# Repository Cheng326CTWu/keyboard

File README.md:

# 65% keyboard

## Overview

This project was made with the intention of familiarizing myself with the work flow of KiCad. It was also a way to re-learn concepts for schematic captures and the different considerations when laying out a PCB. This repo contains a 65% keyboard PCB design made by referencing tutorials and modifying with new components.

## Software Requirement

* KiCAD

## Tutorial Reference Links

* [RuiQiMao's keyboard tutorial](https://github.com/ruiqimao/keyboard-pcb-guide)
* [ai03's keyboard tutorial](https://wiki.ai03.com/books/pcb-design/page/pcb-guide-part-1---preparations)

## Reference Links

* [Discipline's keyboard repo](https://github.com/coseyfannitutti/discipline)
* [Layer definition in KiCad](https://forum.kicad.info/t/what-is-the-meaning-of-the-layers-in-pcb-new-and-in-the-footprint-editor/9688)
* [BOM in KiCad](https://forum.kicad.info/t/how-to-create-a-bill-of-materials-bom/12346)

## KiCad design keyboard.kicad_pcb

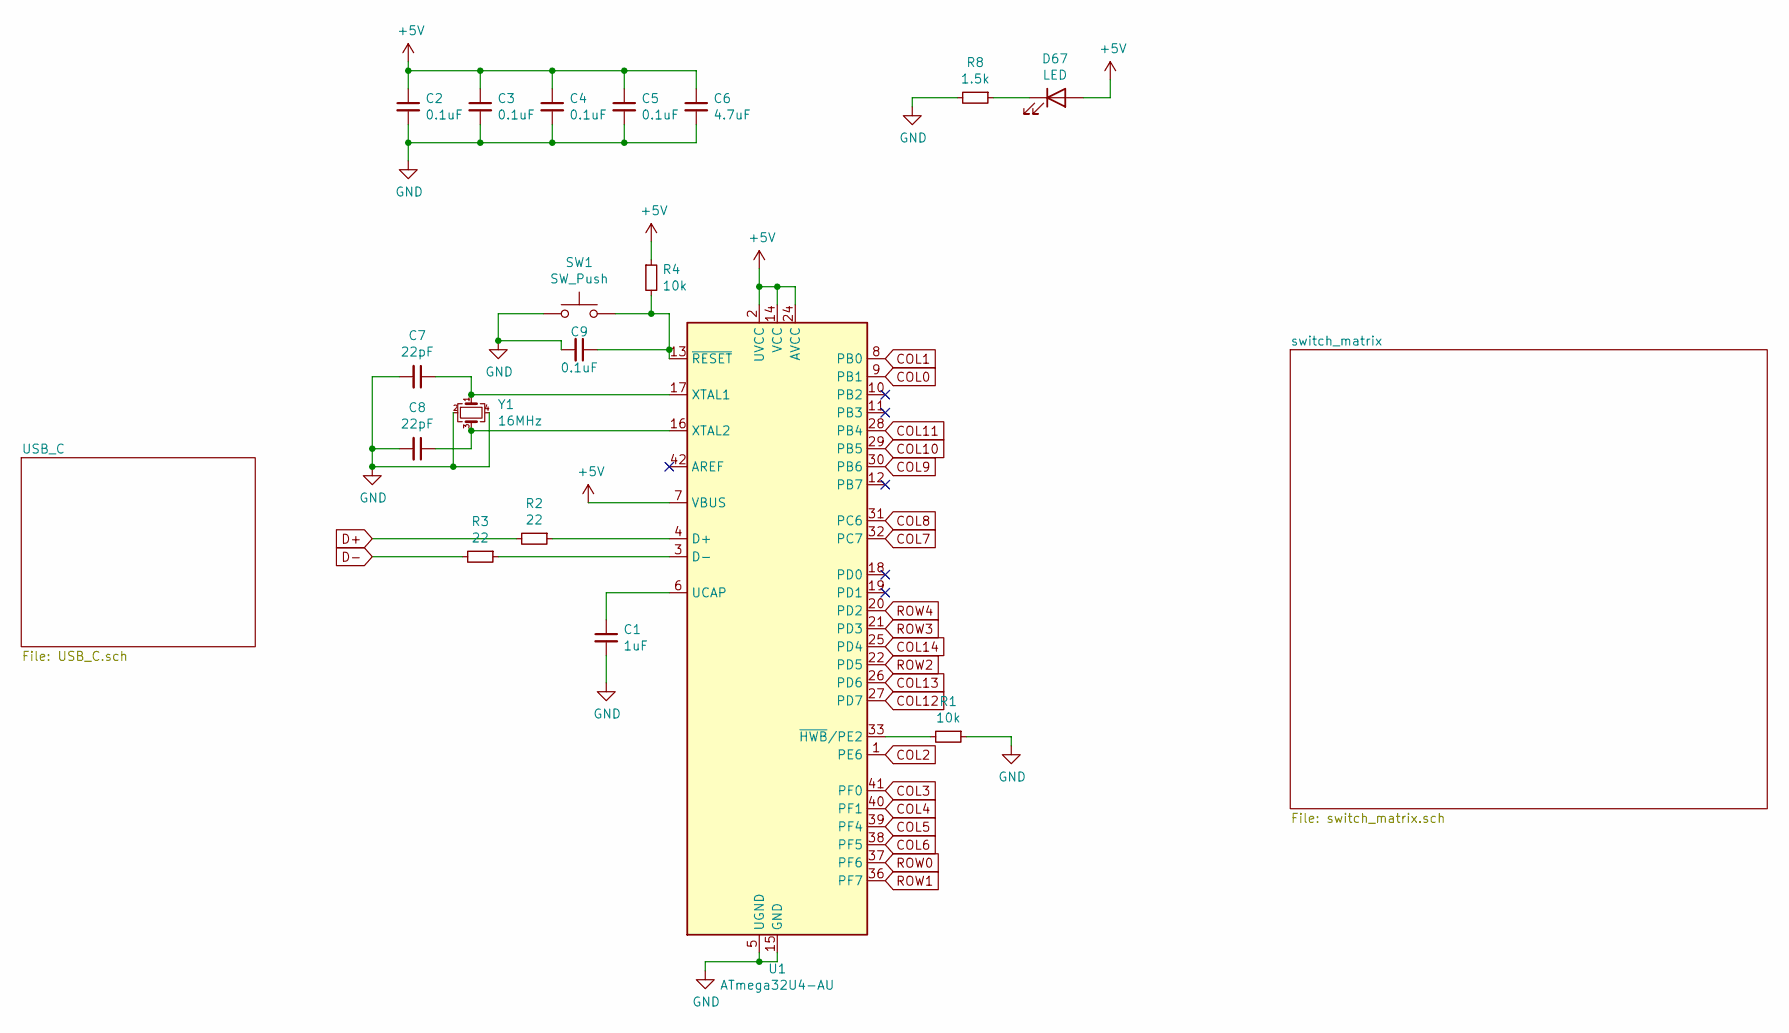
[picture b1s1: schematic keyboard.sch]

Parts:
C1: 1uF; C_0805_2012Metric
C2, C3, C4, C5, C9: 0.1uF; C_0805_2012Metric
C6: 4.7uF; C_0805_2012Metric
C7, C8: 22pF; C_0805_2012Metric
D67: LED; LED_0805_2012Metric
R1, R4: 10k; R_0805_2012Metric
R2, R3: 22; R_0805_2012Metric
R8: 1.5k; R_0805_2012Metric
SW1: SW_Push; SKQG-1155865
U1: ATmega32U4-AU; TQFP-44_10x10mm_P0.8mm
Y1: 16MHz; Crystal_SMD_3225-4Pin_3.2x2.5mm

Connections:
+5V: C2.1, C3.1, C4.1, C5.1, C6.1, D67.2 (A), R4.1, U1.2 (UVCC), U1.7 (VBUS), U1.14 (VCC), U1.24 (AVCC), U1.34 (VCC), U1.44 (AVCC); also elsewhere on the board
COL0: U1.9 (PB1); also elsewhere on the board
COL1: U1.8 (PB0); also elsewhere on the board
COL2: U1.1 (PE6); also elsewhere on the board
COL3: U1.41 (PF0); also elsewhere on the board
COL4: U1.40 (PF1); also elsewhere on the board
COL5: U1.39 (PF4); also elsewhere on the board
COL6: U1.38 (PF5); also elsewhere on the board
COL7: U1.32 (PC7); also elsewhere on the board
COL8: U1.31 (PC6); also elsewhere on the board
COL9: U1.30 (PB6); also elsewhere on the board
COL10: U1.29 (PB5); also elsewhere on the board
COL11: U1.28 (PB4); also elsewhere on the board
COL12: U1.27 (PD7); also elsewhere on the board
COL13: U1.26 (PD6); also elsewhere on the board
COL14: U1.25 (PD4); also elsewhere on the board
D+: R2.2; also elsewhere on the board
D-: R3.2; also elsewhere on the board
GND: C1.2, C2.2, C3.2, C4.2, C5.2, C6.2, C7.2, C8.2, C9.2, R1.1, R8.2, SW1.1, U1.5 (UGND), U1.15 (GND), U1.23 (GND), U1.35 (GND), U1.43 (GND), Y1.2, Y1.4; also elsewhere on the board
unnamed: C1.1, U1.6 (UCAP)
unnamed: C7.1, U1.17 (XTAL1), Y1.1
unnamed: C8.1, U1.16 (XTAL2), Y1.3
unnamed: C9.1, R4.2, SW1.2, U1.13 (~RESET)
unnamed: D67.1 (K), R8.1
unnamed: R1.2, U1.33 (~HWB~/PE2)
unnamed: R2.1, U1.4 (D+)
unnamed: R3.1, U1.3 (D-)
ROW0: U1.37 (PF6); also elsewhere on the board
ROW1: U1.36 (PF7); also elsewhere on the board
ROW2: U1.22 (PD5); also elsewhere on the board
ROW3: U1.21 (PD3); also elsewhere on the board
ROW4: U1.20 (PD2); also elsewhere on the board

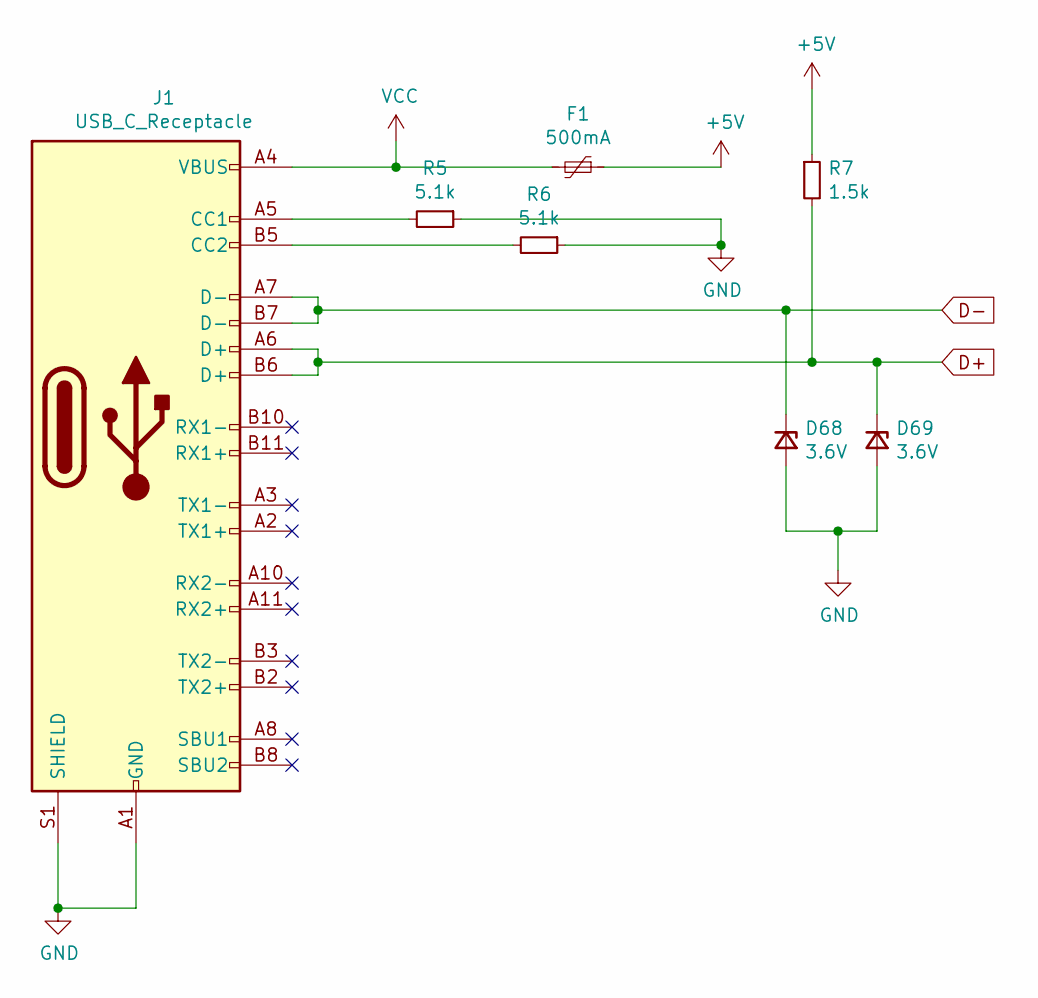
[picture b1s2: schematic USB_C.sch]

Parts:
D68, D69: 3.6V; D_0805_2012Metric
F1: 500mA; Fuse_1206_3216Metric
J1: USB_C_Receptacle; USB_C_Receptacle_GCT_USB4085
R5, R6: 5.1k; R_0805_2012Metric
R7: 1.5k; R_0805_2012Metric

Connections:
+5V: F1.1, R7.1; also elsewhere on the board
D+: D69.1 (K), J1.A6 (D+), J1.B6 (D+), R7.2; also elsewhere on the board
D-: D68.1 (K), J1.A7 (D-), J1.B7 (D-); also elsewhere on the board
GND: D68.2 (A), D69.2 (A), J1.A1 (GND), J1.A12 (GND), J1.B1 (GND), J1.B12 (GND), J1.S1 (SHIELD), R5.1, R6.1; also elsewhere on the board
unnamed: J1.A5 (CC1), R5.2
unnamed: J1.B5 (CC2), R6.2
VCC: F1.2, J1.A4 (VBUS), J1.A9 (VBUS), J1.B4 (VBUS), J1.B9 (VBUS)

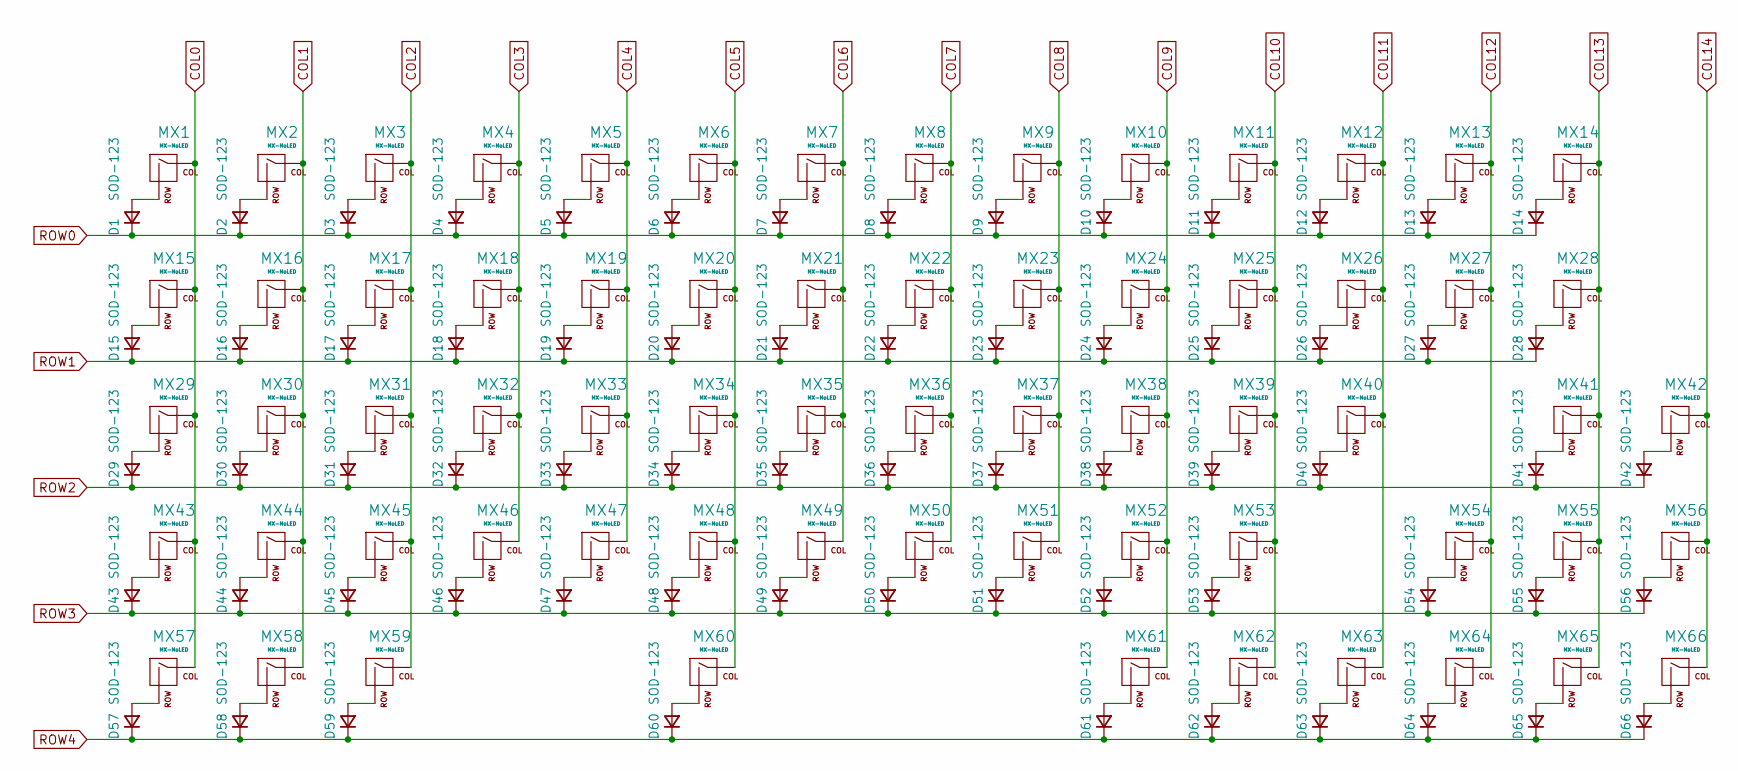
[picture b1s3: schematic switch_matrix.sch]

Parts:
D1, D2, D3, D4, D5, D6, D7, D8, D9, D10, D11, D12, D13, D14, D15, D16, D17, D18, D19, D20, D21, D22, D23, D24, D25, D26, D27, D28, D29, D30, D31, D32, D33, D34, D35, D36, D37, D38, D39, D40, D41, D42, D43, D44, D45, D46, D47, D48, D49, D50, D51, D52, D53, D54, D55, D56, D57, D58, D59, D60, D61, D62, D63, D64, D65, D66: SOD-123; D_SOD-123
MX1, MX2, MX3, MX4, MX5, MX6, MX7, MX8, MX9, MX10, MX11, MX12, MX13, MX16, MX17, MX18, MX19, MX20, MX21, MX22, MX23, MX24, MX25, MX26, MX27, MX30, MX31, MX32, MX33, MX34, MX35, MX36, MX37, MX38, MX39, MX40, MX42, MX44, MX45, MX46, MX47, MX48, MX49, MX50, MX51, MX52, MX53, MX55, MX56, MX58, MX64, MX65, MX66: MX-NoLED; MXOnly-1U-Hotswap
MX14: MX-NoLED; MXOnly-2U-Hotswap
MX15, MX28: MX-NoLED; MXOnly-1.5U-Hotswap
MX29: MX-NoLED; MXOnly-1.75U-Hotswap
MX41, MX43, MX54: MX-NoLED; MXOnly-2.25U-Hotswap
MX57, MX59, MX61, MX62, MX63: MX-NoLED; MXOnly-1.25U-Hotswap
MX60: MX-NoLED; MXOnly-6.25U-Hotswap

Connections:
COL0: MX1.1 (COL), MX15.1 (COL), MX29.1 (COL), MX43.1 (COL), MX57.1 (COL); also elsewhere on the board
COL1: MX2.1 (COL), MX16.1 (COL), MX30.1 (COL), MX44.1 (COL), MX58.1 (COL); also elsewhere on the board
COL2: MX3.1 (COL), MX17.1 (COL), MX31.1 (COL), MX45.1 (COL), MX59.1 (COL); also elsewhere on the board
COL3: MX4.1 (COL), MX18.1 (COL), MX32.1 (COL), MX46.1 (COL); also elsewhere on the board
COL4: MX5.1 (COL), MX19.1 (COL), MX33.1 (COL), MX47.1 (COL); also elsewhere on the board
COL5: MX6.1 (COL), MX20.1 (COL), MX34.1 (COL), MX48.1 (COL), MX60.1 (COL); also elsewhere on the board
COL6: MX7.1 (COL), MX21.1 (COL), MX35.1 (COL), MX49.1 (COL); also elsewhere on the board
COL7: MX8.1 (COL), MX22.1 (COL), MX36.1 (COL), MX50.1 (COL); also elsewhere on the board
COL8: MX9.1 (COL), MX23.1 (COL), MX37.1 (COL), MX51.1 (COL); also elsewhere on the board
COL9: MX10.1 (COL), MX24.1 (COL), MX38.1 (COL), MX52.1 (COL), MX61.1 (COL); also elsewhere on the board
COL10: MX11.1 (COL), MX25.1 (COL), MX39.1 (COL), MX53.1 (COL), MX62.1 (COL); also elsewhere on the board
COL11: MX12.1 (COL), MX26.1 (COL), MX40.1 (COL), MX63.1 (COL); also elsewhere on the board
COL12: MX13.1 (COL), MX27.1 (COL), MX54.1 (COL), MX64.1 (COL); also elsewhere on the board
COL13: MX14.1 (COL), MX28.1 (COL), MX41.1 (COL), MX55.1 (COL), MX65.1 (COL); also elsewhere on the board
COL14: MX42.1 (COL), MX56.1 (COL), MX66.1 (COL); also elsewhere on the board
unnamed: D1.2 (A), MX1.2 (ROW)
unnamed: D2.2 (A), MX2.2 (ROW)
unnamed: D3.2 (A), MX3.2 (ROW)
unnamed: D4.2 (A), MX4.2 (ROW)
unnamed: D5.2 (A), MX5.2 (ROW)
unnamed: D6.2 (A), MX6.2 (ROW)
unnamed: D7.2 (A), MX7.2 (ROW)
unnamed: D8.2 (A), MX8.2 (ROW)
unnamed: D9.2 (A), MX9.2 (ROW)
unnamed: D10.2 (A), MX10.2 (ROW)
unnamed: D11.2 (A), MX11.2 (ROW)
unnamed: D12.2 (A), MX12.2 (ROW)
unnamed: D13.2 (A), MX13.2 (ROW)
unnamed: D14.2 (A), MX14.2 (ROW)
unnamed: D15.2 (A), MX15.2 (ROW)
unnamed: D16.2 (A), MX16.2 (ROW)
unnamed: D17.2 (A), MX17.2 (ROW)
unnamed: D18.2 (A), MX18.2 (ROW)
unnamed: D19.2 (A), MX19.2 (ROW)
unnamed: D20.2 (A), MX20.2 (ROW)
unnamed: D21.2 (A), MX21.2 (ROW)
unnamed: D22.2 (A), MX22.2 (ROW)
unnamed: D23.2 (A), MX23.2 (ROW)
unnamed: D24.2 (A), MX24.2 (ROW)
unnamed: D25.2 (A), MX25.2 (ROW)
unnamed: D26.2 (A), MX26.2 (ROW)
unnamed: D27.2 (A), MX27.2 (ROW)
unnamed: D28.2 (A), MX28.2 (ROW)
unnamed: D29.2 (A), MX29.2 (ROW)
unnamed: D30.2 (A), MX30.2 (ROW)
unnamed: D31.2 (A), MX31.2 (ROW)
unnamed: D32.2 (A), MX32.2 (ROW)
unnamed: D33.2 (A), MX33.2 (ROW)
unnamed: D34.2 (A), MX34.2 (ROW)
unnamed: D35.2 (A), MX35.2 (ROW)
unnamed: D36.2 (A), MX36.2 (ROW)
unnamed: D37.2 (A), MX37.2 (ROW)
unnamed: D38.2 (A), MX38.2 (ROW)
unnamed: D39.2 (A), MX39.2 (ROW)
unnamed: D40.2 (A), MX40.2 (ROW)
unnamed: D41.2 (A), MX41.2 (ROW)
unnamed: D42.2 (A), MX42.2 (ROW)
unnamed: D43.2 (A), MX43.2 (ROW)
unnamed: D44.2 (A), MX44.2 (ROW)
unnamed: D45.2 (A), MX45.2 (ROW)
unnamed: D46.2 (A), MX46.2 (ROW)
unnamed: D47.2 (A), MX47.2 (ROW)
unnamed: D48.2 (A), MX48.2 (ROW)
unnamed: D49.2 (A), MX49.2 (ROW)
unnamed: D50.2 (A), MX50.2 (ROW)
unnamed: D51.2 (A), MX51.2 (ROW)
unnamed: D52.2 (A), MX52.2 (ROW)
unnamed: D53.2 (A), MX53.2 (ROW)
unnamed: D54.2 (A), MX54.2 (ROW)
unnamed: D55.2 (A), MX55.2 (ROW)
unnamed: D56.2 (A), MX56.2 (ROW)
unnamed: D57.2 (A), MX57.2 (ROW)
unnamed: D58.2 (A), MX58.2 (ROW)
unnamed: D59.2 (A), MX59.2 (ROW)
unnamed: D60.2 (A), MX60.2 (ROW)
unnamed: D61.2 (A), MX61.2 (ROW)
unnamed: D62.2 (A), MX62.2 (ROW)
unnamed: D63.2 (A), MX63.2 (ROW)
unnamed: D64.2 (A), MX64.2 (ROW)
unnamed: D65.2 (A), MX65.2 (ROW)
unnamed: D66.2 (A), MX66.2 (ROW)
ROW0: D1.1 (K), D2.1 (K), D3.1 (K), D4.1 (K), D5.1 (K), D6.1 (K), D7.1 (K), D8.1 (K), D9.1 (K), D10.1 (K), D11.1 (K), D12.1 (K), D13.1 (K), D14.1 (K); also elsewhere on the board
ROW1: D15.1 (K), D16.1 (K), D17.1 (K), D18.1 (K), D19.1 (K), D20.1 (K), D21.1 (K), D22.1 (K), D23.1 (K), D24.1 (K), D25.1 (K), D26.1 (K), D27.1 (K), D28.1 (K); also elsewhere on the board
ROW2: D29.1 (K), D30.1 (K), D31.1 (K), D32.1 (K), D33.1 (K), D34.1 (K), D35.1 (K), D36.1 (K), D37.1 (K), D38.1 (K), D39.1 (K), D40.1 (K), D41.1 (K), D42.1 (K); also elsewhere on the board
ROW3: D43.1 (K), D44.1 (K), D45.1 (K), D46.1 (K), D47.1 (K), D48.1 (K), D49.1 (K), D50.1 (K), D51.1 (K), D52.1 (K), D53.1 (K), D54.1 (K), D55.1 (K), D56.1 (K); also elsewhere on the board
ROW4: D57.1 (K), D58.1 (K), D59.1 (K), D60.1 (K), D61.1 (K), D62.1 (K), D63.1 (K), D64.1 (K), D65.1 (K), D66.1 (K); also elsewhere on the board

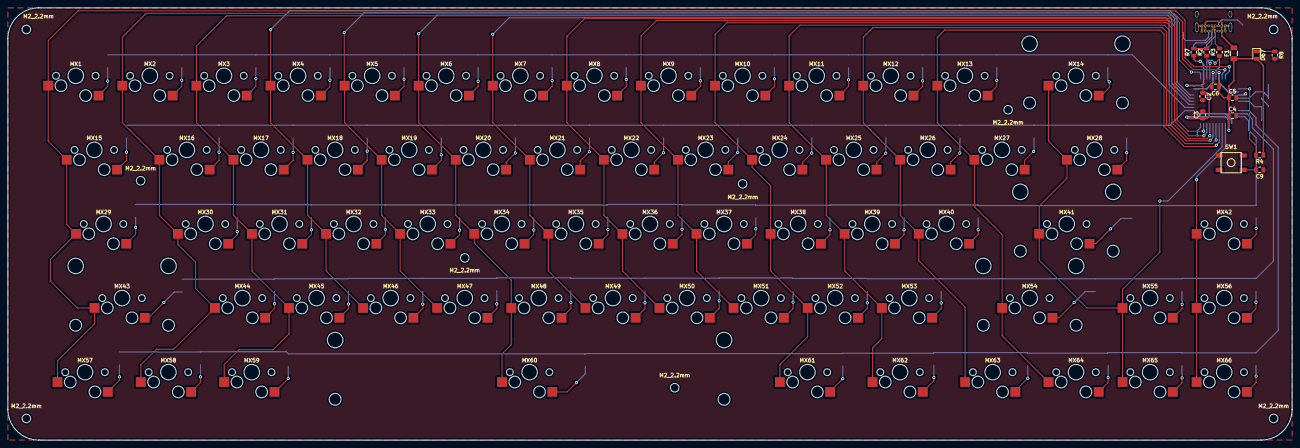
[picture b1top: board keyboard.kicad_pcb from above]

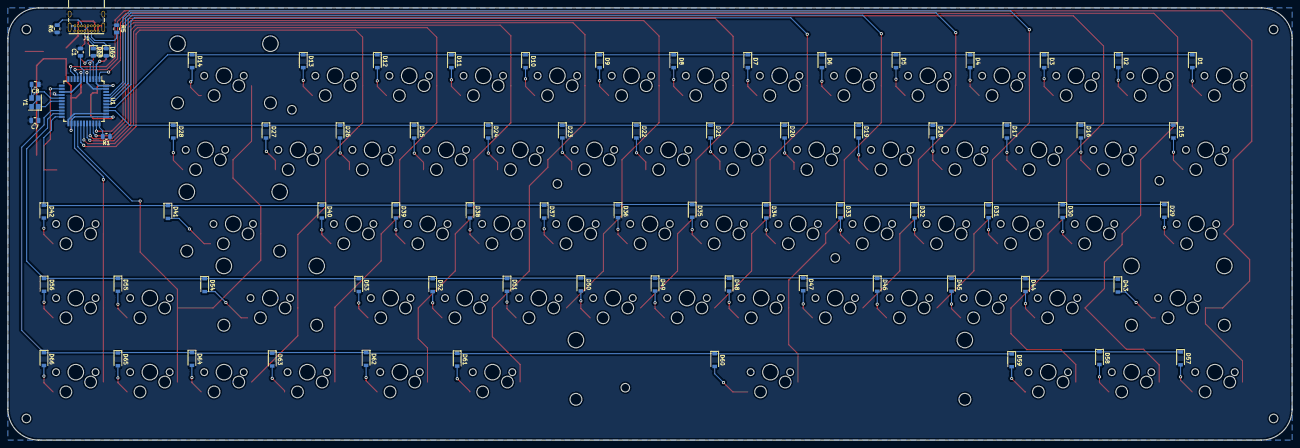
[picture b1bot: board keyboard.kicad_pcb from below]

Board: 2 copper layers, 330.2 x 111.1 mm, 166 parts (143 on the bottom side), 101 nets.

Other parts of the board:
M2_2.2mm, M2_2.2mm#2, M2_2.2mm#3, M2_2.2mm#4, M2_2.2mm#5, M2_2.2mm#6, M2_2.2mm#7, M2_2.2mm#8, M2_2.2mm#9: MountingHole_2.2mm_M2

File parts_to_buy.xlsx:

Components | Quantity | Value | Package | Sample parts link | Comment
C1 | 1 | 1uF | 0805 | https://www.digikey.ca/en/products/detail/samsung-electro-me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
C2, C3, C4, C5, C9 | 5 | 0.1uF | 0805 | https://www.digikey.ca/en/products/detail/samsung-electro-me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
C6 | 1 | 4.7uF | 0805 | https://www.digikey.ca/en/products/detail/yageo/CC0805KKX5R5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
C7, C8 | 2 | 22pF | 0805 | https://www.digikey.ca/en/products/detail/samsung-electro-me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
D1, D2, D3, D4, D5, D6, D7, D8, D9, D10, D11, D12, D13, D14, D15, D16, D17, D18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 | 66 | SOD-123 | SOD-123 | https://www.digikey.com/product-detail/en/micro-commercial-c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
D67 | 1 | LED | 0805 | https://www.digikey.ca/en/products/detail/broadcom-limited/H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
D68, D69 | 2 | 3.6V | 0805 | https://www.digikey.ca/en/products/detail/diodes-incorporate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
 |  |  |  | https://www.digikey.ca/en/products/detail/rohm-semiconductor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 | This one is alternative, as the breakdown voltage range is a bit too big.
F1 | 1 | 500mA | 1206 | https://www.digikey.ca/en/products/detail/bel-fuse-inc/0ZCJ0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
J1 | 1 | USB_C_Receptacle | GCT USB4085 | https://www.digikey.ca/en/products/detail/gct/USB4085-GF-A/9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
MX1, MX2, MX3, MX4, MX5, MX6, MX7, MX8, MX9, MX10, MX11, MX12, MX13, MX16, MX17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 | 53 | MX-NoLED
MX14 | 1 | MX-NoLED
MX15, MX28 | 2 | MX-NoLED
MX29 | 1 | MX-NoLED
MX41, MX43, MX54 | 3 | MX-NoLED
MX57, MX59, MX61, MX62, MX63 | 5 | MX-NoLED
MX60 | 1 | MX-NoLED
R1, R4 | 2 | 10k | 0805 | https://www.digikey.com/product-detail/en/panasonic-electron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
R2, R3 | 2 | 22 | 0805 | https://www.digikey.com/product-detail/en/panasonic-electron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
R5, R6 | 2 | 5.1k | 0805 | https://www.digikey.ca/en/products/detail/yageo/RT0805DRE075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
R7, R8 | 2 | 1.5k | 0805 | https://www.digikey.ca/en/products/detail/yageo/RE0805FRE071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
SW1 | 1 | SW_Push | 5.2x5.2mm | https://www.digikey.ca/en/products/detail/c-k/RS-187R05A2-DS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
U1 | 1 | ATmega32U4-AU | 44TQFP 10x10mm | https://www.digikey.ca/en/products/detail/microchip-technolo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
Y1 | 1 | 16MHz | 3.2x2.5mm 4 pads | https://www.digikey.ca/en/products/detail/kyocera-internatio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

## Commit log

2020-07-21 Add submodules
2020-07-21 Added schematic and footprint library
2020-07-21 Wired MCU and USB C
2020-07-21 Fix README
2020-07-21 Renamed keyboard_matrix to switch_matrix
2020-07-21 Delete keyboard_matrix.sch
    keyboard_matrix was renamed to switch_matrix but file was not deleted in repo
2020-07-21 Wired switch matrix
2020-07-22 Assigned footprint
2020-07-22 Rough layout of PCB
2020-07-23 Changed PCB layout
2020-07-27 Finished routing, filled in ground planes, checked with DRC and 3D render
2020-07-27 adjusted mounting holes, added dimension lines
2020-07-28 Added BOM
2020-07-28 generated gerber and drill files
2020-07-28 created gerber zip file
